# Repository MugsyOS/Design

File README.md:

# Design
All the parts! CAD, PCB and STL files for all of Mugsy's physical components. 

# Mech Control PCB
### Files:
* ****Schematic:**** mech-control-SCH-v0.2.fsch
* ****Board:**** mech-control-BRD-v0.2.fbrd
- - -

# Cone Mech
### Files:
* **Cone Pulley (2 files):** Print main and top.
* **Cone Support (1 file):** Print two for both left and right supports.
* **Stepper Motor Mount (1 file)**: Print one
* **Panels:** 
  * STLs provided for both top and bottom panels.
  * DXF files provided for those with access to a laser or CNC. We use 3mm cast acrylic which works out great. Other material can be used but must be 3mm. 
* **Idler Mount (1 File):** Print two.
- - -
### Additional Parts:
* **Stepper Motor**
  * Model:14HR05-0504S
  * Step Angle: 0.9deg
  * Single Unit Source: [STEPPERONLINE](https://www.omc-stepperonline.com/round-nema-14-bipolar-0-9deg-7ncm-9-91oz-in-0-5a-8-5v-36x12mm-4-wires-14hr05-0504s)
* **Signal** **Breakout PCB**: PCB files will be uploaded shortly. Single PCBs will also be available on the web store end of March 2024. 
* **Ethernet Socket:** RJ45 Connector, PCB Mount
* **M3 Threaded Inserts:**
  * Size: M3*4.6x5.7mm
* **M3 x 8mm Hex Head Machine Screws**
* **2GT Timing Pulley:** 
  * Type: 2M-AF
  * 20 Teeth
  * 6mm bore size
* **GT2 Toothless  Idler Pulleys (2x):** 3mm bore size
- - -
# Spout Mech
### Files:
* ****Spout Pulley Assembly (2 files):**** Print main and cap.
* ****Spout Pulley Assembly (2 files):**** Print main and cap.
* ****Spout Arm(1 file)****: Print one
- - -
### Additional Parts:
* ****Stepper Motor****
  * Model: 17HS08-1004S |
  * Step Angle: 1.8 deg
  * Single Unit Source: [STEPPERONLINE](https://www.omc-stepperonline.com/nema-17-bipolar-1-8deg-16ncm-22-6oz-in-1a-3-7v-42x42x20mm-4-wires-17hs08-1004s)
* ****M8 x 50mm Threaded Rod****
* ****8mm Shaft Lock Collar:**** 
  * 8mm(ID) * 14mm (OD) * 7mm (Depth)
* ****2GT Timing Pulley:****
  * 40 Teeth 
  * 8mm Bore Size
* ****GT2 Belt:**** 
  * 156mm * 6mm
- - -
# Screen Mount/Stabilizer
### Files:
* ****Screen Support:**** Left Side (single)
* ****Screen Support:**** Right Side (double)
* ****Screen Mount Main****: Print one
- - -
****All STEP/Fusion CAD source files will be uploaded as soon as possible.****

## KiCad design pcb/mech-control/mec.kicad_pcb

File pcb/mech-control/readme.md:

**Components:**
* Nano Microcontroller
* 2x DRV8825 Stepper Drivers
* 2x10 pin headers for IO bridge
* 12v input
* 12v pass through
* 2x 47uf electrolytic capacitors
* 3x 100nf decoupling capacitors
* RJ45 Jack for connecting cone mech
* TRRS Jack for connecting spout

⠀**IO Bridge:** The IO bridge exposes all of the unused Nano’s pins except for reset and VIN:
* 2x 3V3
* 2x 5V
* 4x GND
* A0
* A1
* A2
* A4 / SDA
* A5 / SCL
* A6
* A7
* D0
* D1
* D12
* D13
* AREF

All of the analog pins can also be used as digital pins as needed.
**Board Files:** The schematic and board files have been uploaded to the design repo here.

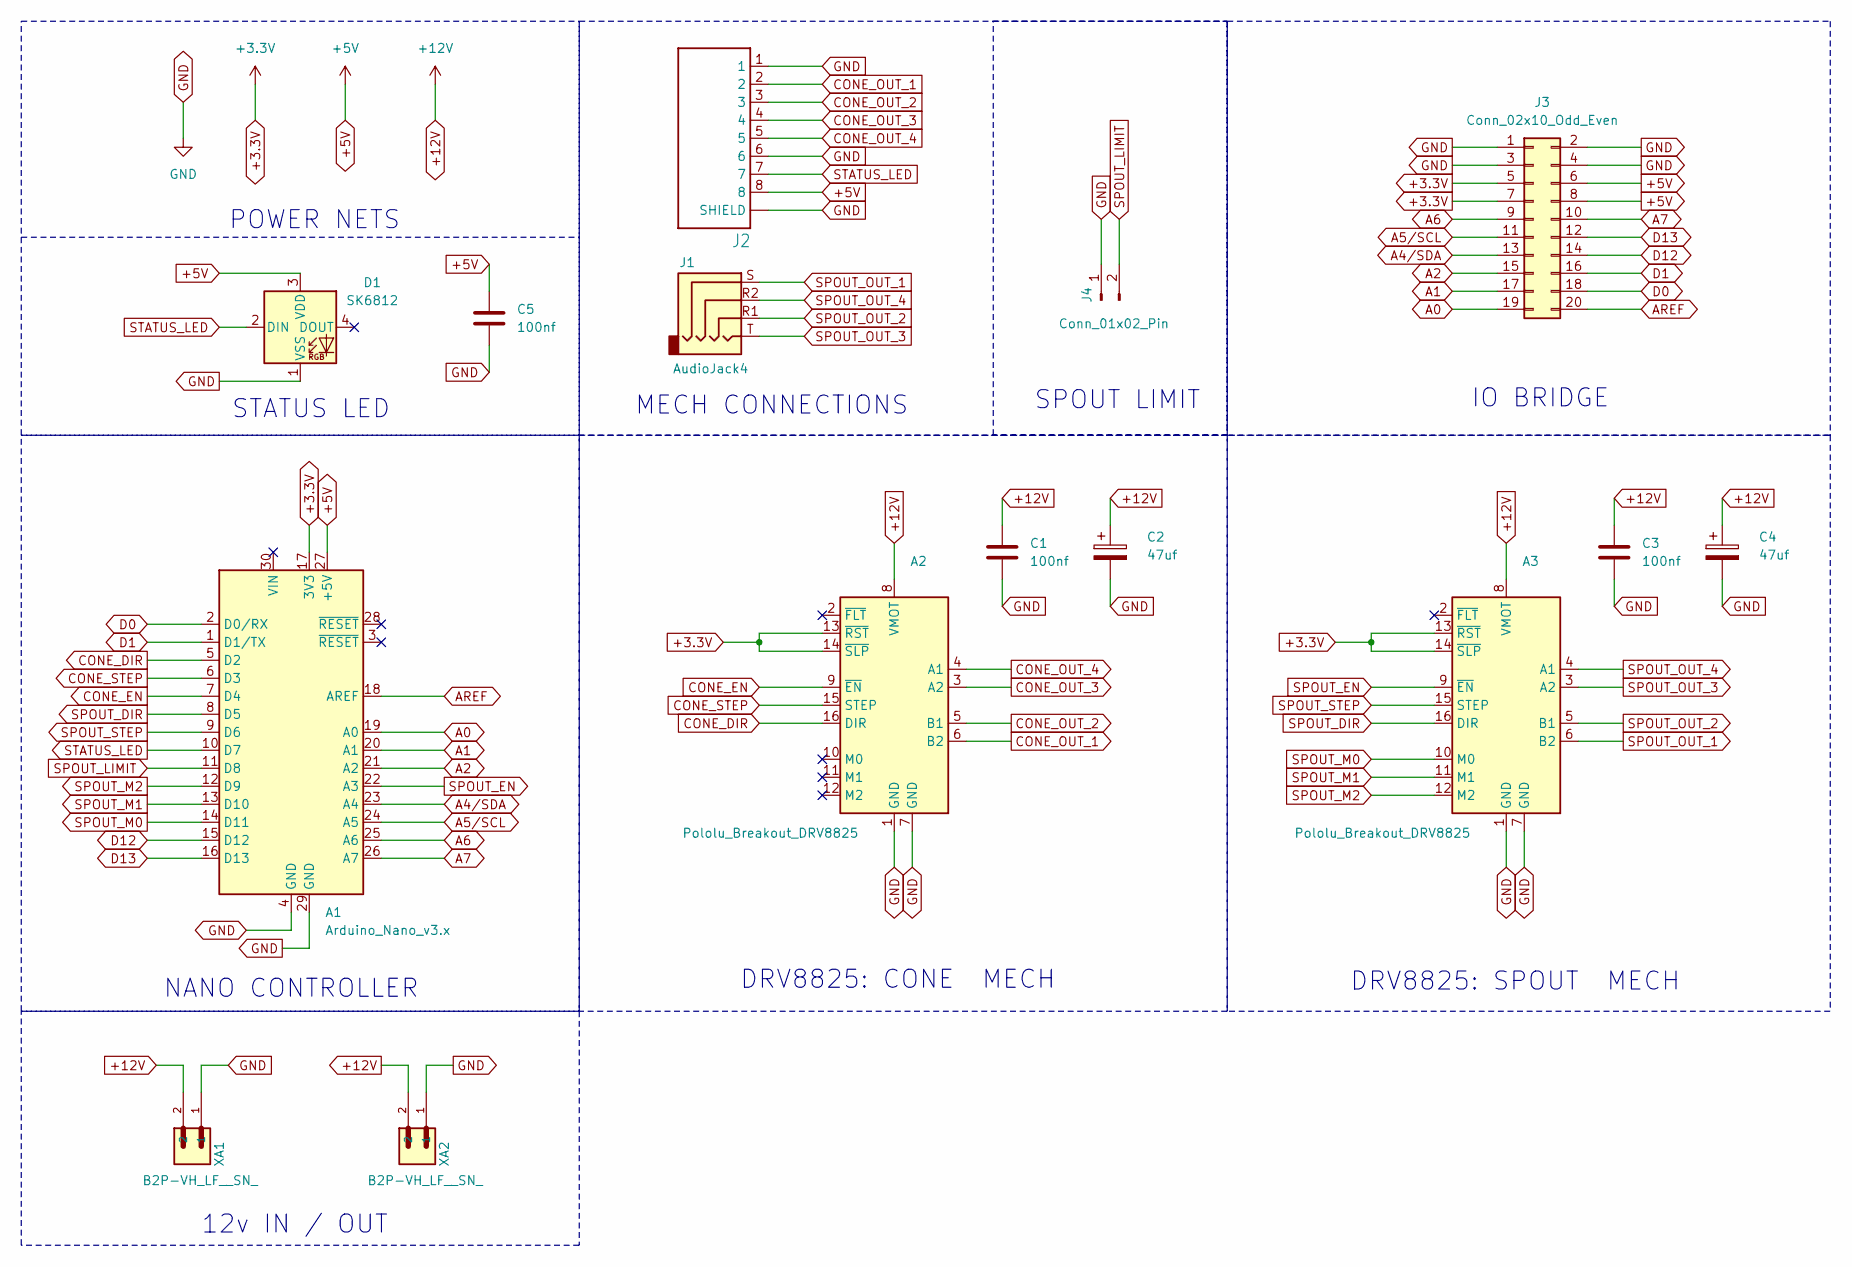
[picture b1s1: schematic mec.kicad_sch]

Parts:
A1: Arduino_Nano_v3.x; Arduino_Nano
A2, A3: Pololu_Breakout_DRV8825; Pololu_Breakout-16_15.2x20.3mm
C1, C3, C5: 100nf; C_0805_2012Metric
C2, C4: 47uf; CP_Elec_6.3x7.7
D1: SK6812; LED_SK6812_PLCC4_5.0x5.0mm_P3.2mm
J1: AudioJack4; Jack_3.5mm_KoreanHropartsElec_PJ-320D-4A_Horizontal
J2: MUGSY_RJ45-8N-B
J3: Conn_02x10_Odd_Even; PinHeader_2x10_P2.54mm_Vertical
J4: Conn_01x02_Pin; JST_XH_B2B-XH-A_1x02_P2.50mm_Vertical
XA1, XA2: B2P-VH_LF__SN_; JST_B2P-VH_LF__SN_

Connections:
+3.3V: A1.17 (3V3), A2.13 (~RST), A2.14 (~SLP), A3.13 (~RST), A3.14 (~SLP), J3.5, J3.7
+5V: A1.27 (+5V), C5.1, D1.3 (VDD), J2.8, J3.6, J3.8
+12V: A2.8 (VMOT), A3.8 (VMOT), C1.1, C2.1, C3.1, C4.1, XA1.2, XA2.2
A0: A1.19 (A0), J3.19
A1: A1.20 (A1), J3.17
A2: A1.21 (A2), J3.15
A4/SDA: A1.23 (A4), J3.13
A5/SCL: A1.24 (A5), J3.11
A6: A1.25 (A6), J3.9
A7: A1.26 (A7), J3.10
AREF: A1.18 (AREF), J3.20
CONE_DIR: A1.5 (D2), A2.16 (DIR)
CONE_EN: A1.7 (D4), A2.9 (~EN)
CONE_OUT_1: A2.6 (B2), J2.2
CONE_OUT_2: A2.5 (B1), J2.3
CONE_OUT_3: A2.3 (A2), J2.4
CONE_OUT_4: A2.4 (A1), J2.5
CONE_STEP: A1.6 (D3), A2.15 (STEP)
D0: A1.2 (D0/RX), J3.18
D1: A1.1 (D1/TX), J3.16
D12: A1.15 (D12), J3.14
D13: A1.16 (D13), J3.12
GND: A1.4 (GND), A1.29 (GND), A2.1 (GND), A2.7 (GND), A3.1 (GND), A3.7 (GND), C1.2, C2.2, C3.2, C4.2, C5.2, D1.1 (VSS), J2.1, J2.6, J2.9 (SHIELD), J2.10 (SHIELD), J3.1, J3.2, J3.3, J3.4, J4.1, XA1.1, XA2.1
SPOUT_DIR: A1.8 (D5), A3.16 (DIR)
SPOUT_EN: A1.22 (A3), A3.9 (~EN)
SPOUT_LIMIT: A1.11 (D8), J4.2
SPOUT_M0: A1.14 (D11), A3.10 (M0)
SPOUT_M1: A1.13 (D10), A3.11 (M1)
SPOUT_M2: A1.12 (D9), A3.12 (M2)
SPOUT_OUT_1: A3.6 (B2), J1.S
SPOUT_OUT_2: A3.5 (B1), J1.R1
SPOUT_OUT_3: A3.3 (A2), J1.T
SPOUT_OUT_4: A3.4 (A1), J1.R2
SPOUT_STEP: A1.9 (D6), A3.15 (STEP)
STATUS_LED: A1.10 (D7), D1.2 (DIN), J2.7

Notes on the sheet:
12v IN / OUT
SPOUT LIMIT
MECH CONNECTIONS
POWER NETS
NANO CONTROLLER
IO BRIDGE
STATUS LED
DRV8825: SPOUT MECH
DRV8825: CONE MECH

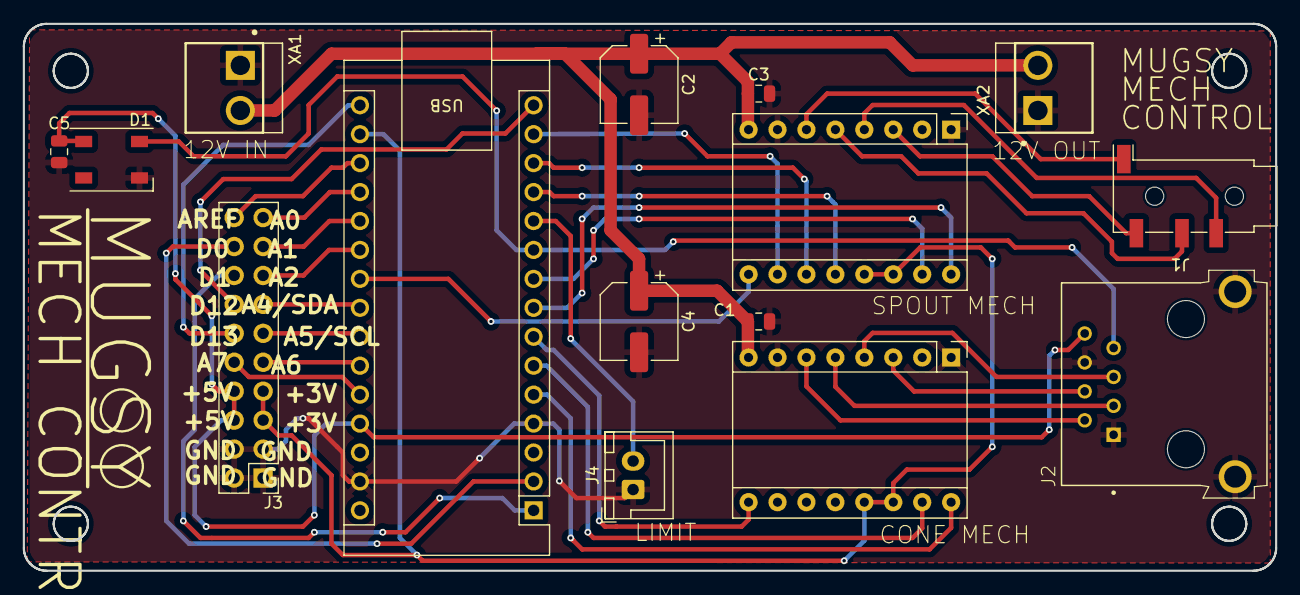
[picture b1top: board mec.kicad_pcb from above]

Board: 2 copper layers, 109.9 x 48.0 mm, 15 parts (0 on the bottom side), 35 nets.

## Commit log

2024-02-29 add mugsy cone mech PCB board and schematic for fusion and eagle
2024-02-29 add .gitignore
2024-06-03 Add kicad schematic and board for Mech Control PCB
2024-07-22 Add spout limit switch
2025-01-01 add spout-v2 stl files
    With the pump switch, the spout has been redesigned to handle the single tube with larger diameter
2025-02-17 add grinder enclosure design files
2025-08-17 Add files via upload
    Add updated enclosure side cone mech tray mount.
2025-09-07 Add README for outer enclosure panels
2025-10-05 Add limit switch mount for new switch position
2026-01-11 add pi pcb mount
